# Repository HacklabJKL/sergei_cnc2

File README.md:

Sergei 2 CNC machine project
============================

This repository contains design files for Hacklab Jyväskylä's CNC machine project.
The machine is built out of existing linear assemblies that have been donated to us, and as such it is not readily reproducible. But some of the modules may be useful and in any case this repository contains information for future maintenance of the machine.

The machine design is a compromise between router and mill designs.
In general router-type CNC machines are more useful for our typical projects, as they have larger work area for flat stock.
But in the same time it would be desirable for the machine to be sturdy enough to cut mild steel at reasonable speeds.

The basic design is similar to fixed gantry routers or a portal milling machine.
X axis ballscrew assembly moves up and down on two Z axis columns.
Y axis moves the table.

Documentation index
-------------------

* [Parts list](PARTS.md)
* [Wiring diagram](electronics/wiring/images/sergei2-wiring.pdf)
* [Usage instructions (wiki)](https://github.com/HacklabJKL/sergei_cnc2/wiki)

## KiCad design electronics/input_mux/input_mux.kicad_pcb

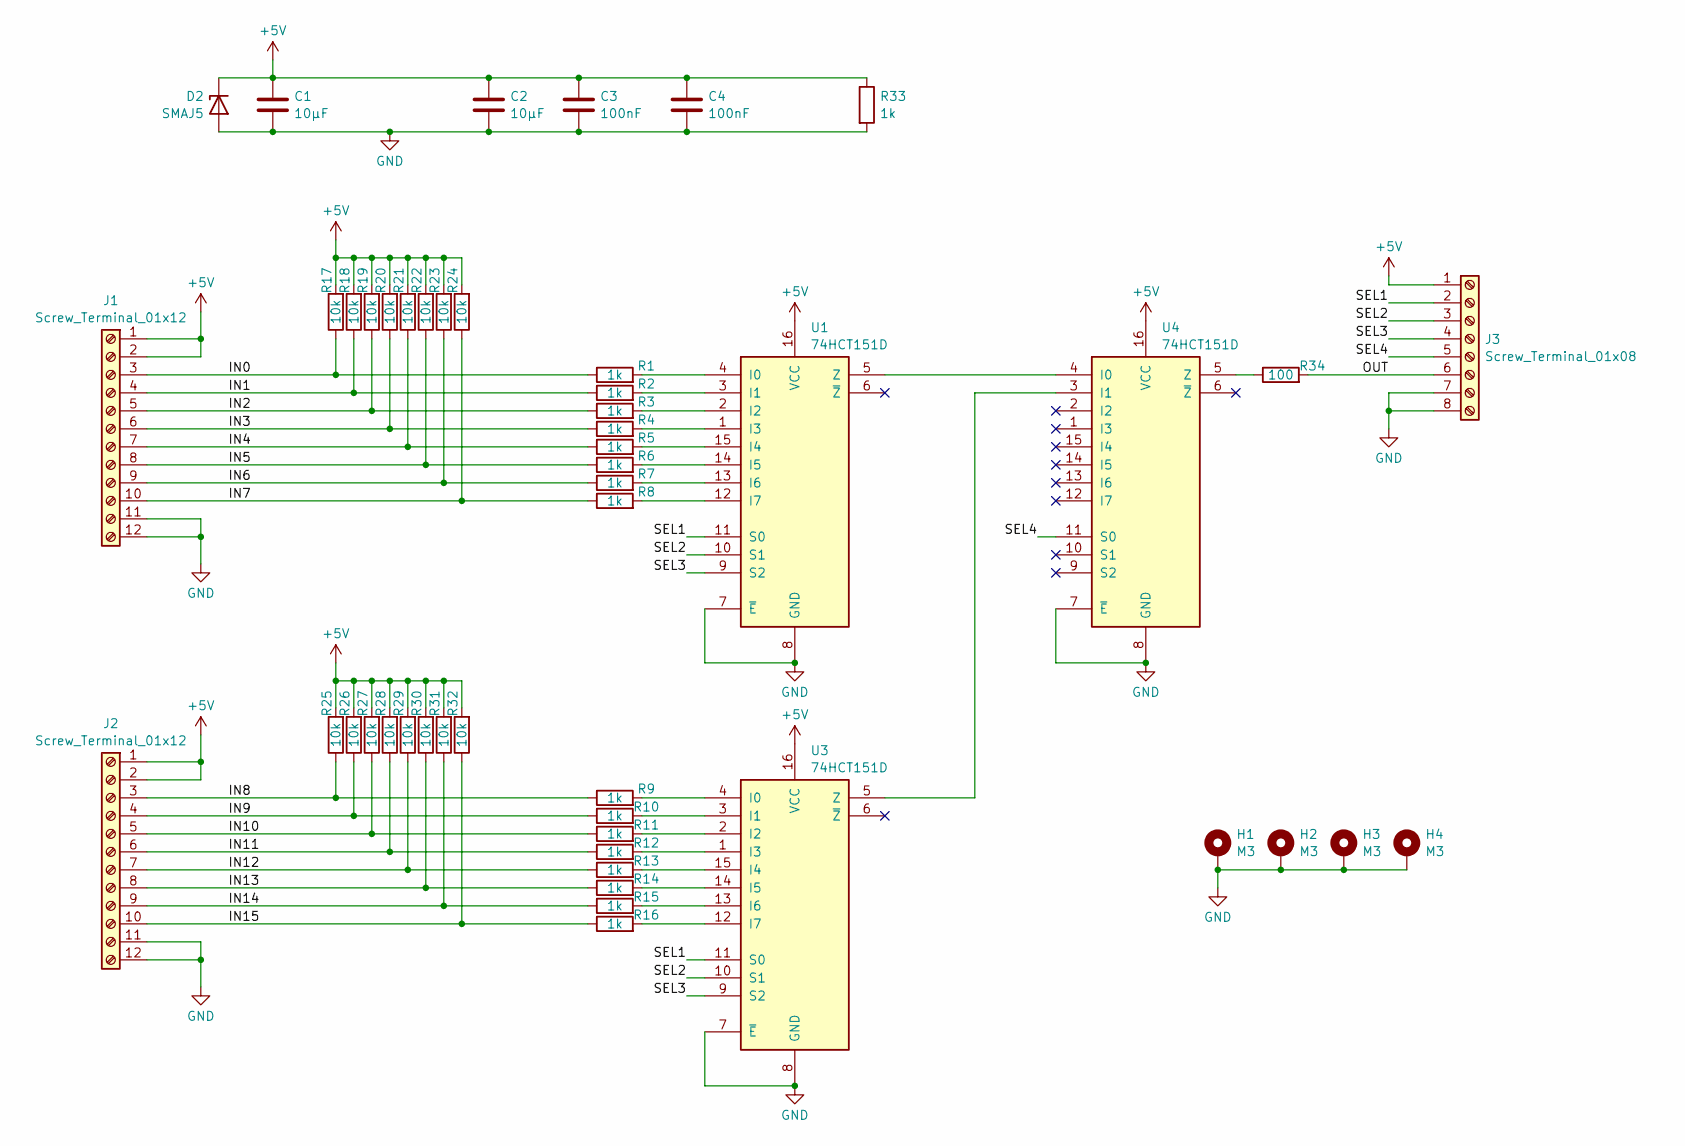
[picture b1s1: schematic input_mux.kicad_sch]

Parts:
C1, C2: 10µF; C_0805_2012Metric
C3, C4: 100nF; C_0805_2012Metric
D2: SMAJ5; D_SMA
H1, H2, H3, H4: M3; MountingHole_3.2mm_M3_Pad
J1, J2: Screw_Terminal_01x12; TerminalBlock_RND_205-00022_1x12_P5.00mm_Horizontal
J3: Screw_Terminal_01x08; TerminalBlock_RND_205-00018_1x08_P5.00mm_Horizontal
R1, R2, R3, R4, R5, R6, R7, R8, R9, R10, R11, R12, R13, R14, R15, R16, R33: 1k; R_0805_2012Metric
R17, R18, R19, R20, R21, R22, R23, R24, R25, R26, R27, R28, R29, R30, R31, R32: 10k; R_0805_2012Metric
R34: 100; R_0805_2012Metric
U1, U3, U4: 74HCT151D; SOIC-16_3.9x9.9mm_P1.27mm

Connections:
+5V: C1.1, C2.1, C3.1, C4.1, D2.1 (K), J1.1, J1.2, J2.1, J2.2, J3.1, R17.2, R18.2, R19.2, R20.2, R21.2, R22.2, R23.2, R24.2, R25.2, R26.2, R27.2, R28.2, R29.2, R30.2, R31.2, R32.2, R33.1, U1.16 (VCC), U3.16 (VCC), U4.16 (VCC)
/IN0: J1.3, R1.1, R17.1
/IN1: J1.4, R2.1, R18.1
/IN2: J1.5, R3.1, R19.1
/IN3: J1.6, R4.1, R20.1
/IN4: J1.7, R5.1, R21.1
/IN5: J1.8, R6.1, R22.1
/IN6: J1.9, R7.1, R23.1
/IN7: J1.10, R8.1, R24.1
/IN8: J2.3, R9.1, R25.1
/IN9: J2.4, R10.1, R26.1
/IN10: J2.5, R11.1, R27.1
/IN11: J2.6, R12.1, R28.1
/IN12: J2.7, R13.1, R29.1
/IN13: J2.8, R14.1, R30.1
/IN14: J2.9, R15.1, R31.1
/IN15: J2.10, R16.1, R32.1
/OUT: J3.6, R34.2
/SEL1: J3.2, U1.11 (S0), U3.11 (S0)
/SEL2: J3.3, U1.10 (S1), U3.10 (S1)
/SEL3: J3.4, U1.9 (S2), U3.9 (S2)
/SEL4: J3.5, U4.11 (S0)
GND: C1.2, C2.2, C3.2, C4.2, D2.2 (A), H1.1, H2.1, H3.1, H4.1, J1.11, J1.12, J2.11, J2.12, J3.7, J3.8, R33.2, U1.7 (~E), U1.8 (GND), U3.7 (~E), U3.8 (GND), U4.7 (~E), U4.8 (GND)
unnamed: R1.2, U1.4 (I0)
unnamed: R2.2, U1.3 (I1)
unnamed: R3.2, U1.2 (I2)
unnamed: R4.2, U1.1 (I3)
unnamed: R5.2, U1.15 (I4)
unnamed: R6.2, U1.14 (I5)
unnamed: R7.2, U1.13 (I6)
unnamed: R8.2, U1.12 (I7)
unnamed: U1.5 (Z), U4.4 (I0)
unnamed: R9.2, U3.4 (I0)
unnamed: R10.2, U3.3 (I1)
unnamed: R11.2, U3.2 (I2)
unnamed: R12.2, U3.1 (I3)
unnamed: R13.2, U3.15 (I4)
unnamed: R14.2, U3.14 (I5)
unnamed: R15.2, U3.13 (I6)
unnamed: R16.2, U3.12 (I7)
unnamed: U3.5 (Z), U4.3 (I1)
unnamed: R34.1, U4.5 (Z)

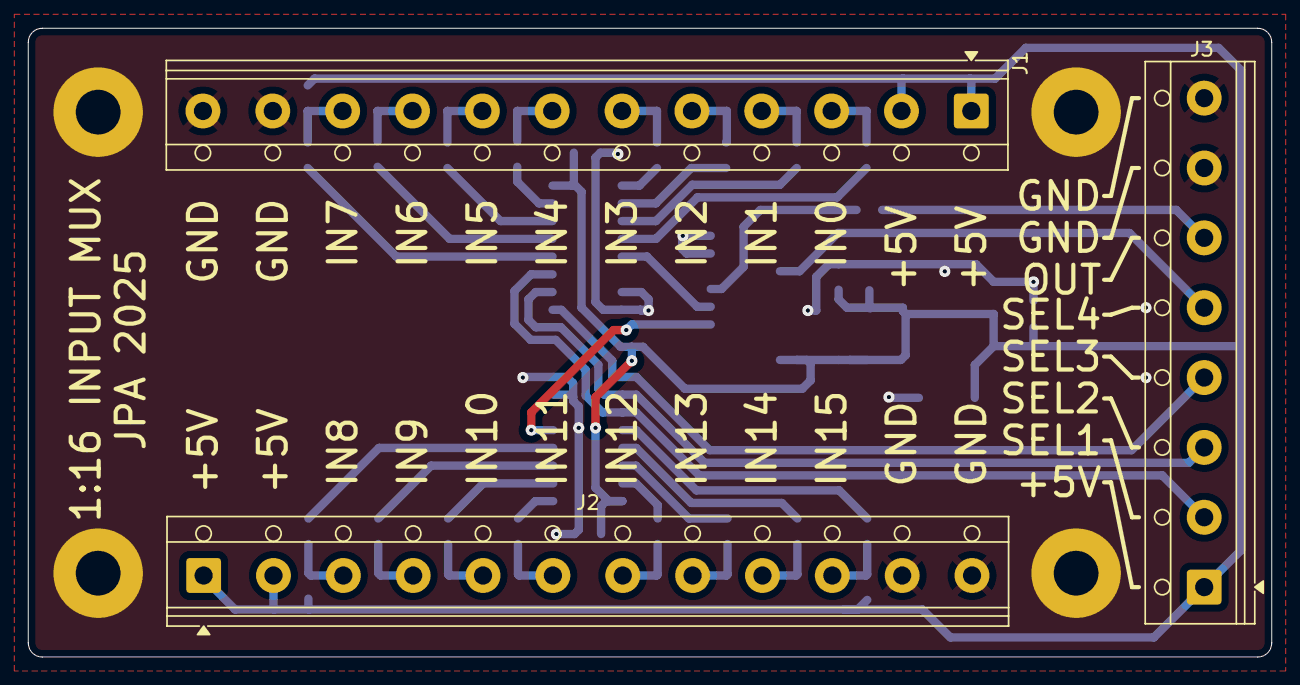
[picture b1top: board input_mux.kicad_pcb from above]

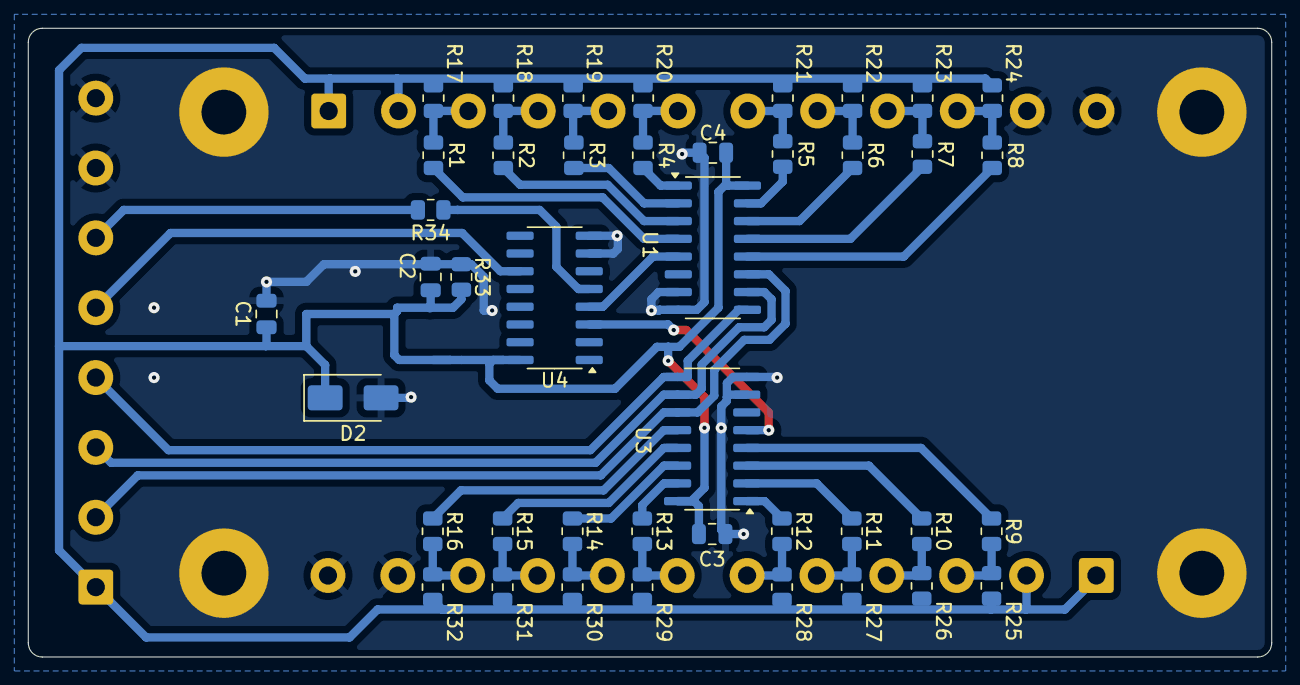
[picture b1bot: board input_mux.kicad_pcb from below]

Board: 2 copper layers, 89.0 x 45.0 mm, 49 parts (42 on the bottom side), 42 nets.

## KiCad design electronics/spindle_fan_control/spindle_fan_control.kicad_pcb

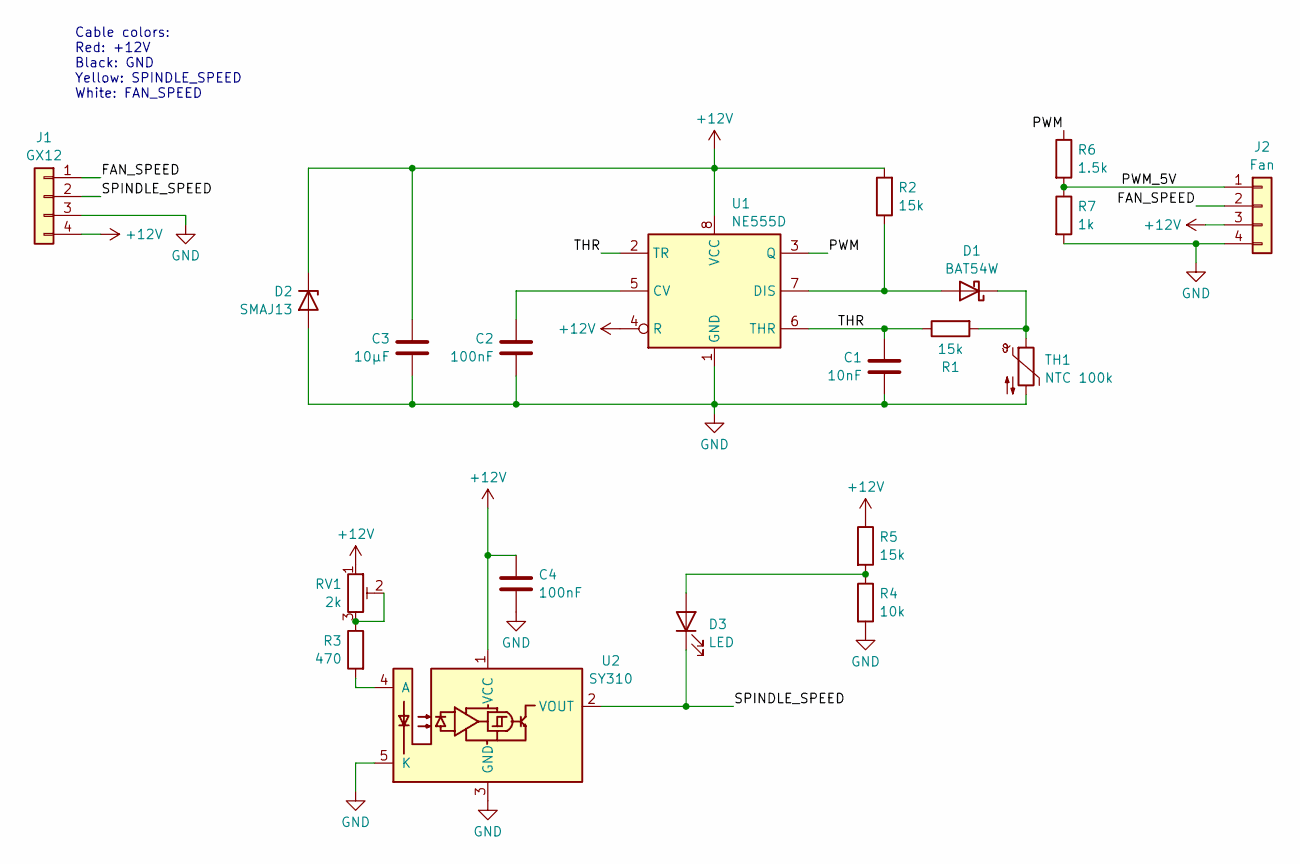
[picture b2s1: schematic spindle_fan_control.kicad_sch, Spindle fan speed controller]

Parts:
C1: 10nF; C_0603_1608Metric
C2, C4: 100nF; C_0603_1608Metric
C3: 10µF; C_0805_2012Metric
D1: BAT54W; D_SOD-123
D2: SMAJ13; D_SMA
D3: LED; D_0603_1608Metric
J1: GX12; PinHeader_2x02_P2.54mm_Vertical
J2: Fan; PinHeader_1x04_P2.54mm_Horizontal
R1, R2, R5: 15k; R_0603_1608Metric
R3: 470; R_0603_1608Metric
R4: 10k; R_0603_1608Metric
R6: 1.5k; R_0603_1608Metric
R7: 1k; R_0603_1608Metric
RV1: 2k; Potentiometer_Bourns_TC33X_Vertical
TH1: NTC 100k; PinHeader_1x02_P2.54mm_Vertical
U1: NE555D; SOIC-8_3.9x4.9mm_P1.27mm
U2: SY310; Kodenshi_LG206D

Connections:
+12V: C3.2, C4.2, D2.1 (K), J1.4, J2.3, R2.2, R5.1, RV1.1, U1.4 (R), U1.8 (VCC), U2.1 (VCC)
/FAN_SPEED: J1.1, J2.2
/PWM: R6.1, U1.3 (Q)
/PWM_5V: J2.1, R6.2, R7.1
/SPINDLE_SPEED: D3.1 (K), J1.2, U2.2 (VOUT)
/THR: C1.1, R1.1, U1.2 (TR), U1.6 (THR)
GND: C1.2, C2.1, C3.1, C4.1, D2.2 (A), J1.3, J2.4, R4.2, R7.2, TH1.2, U1.1 (GND), U2.3 (GND), U2.5 (K)
unnamed: D1.2 (A), R2.1, U1.7 (DIS)
unnamed: D1.1 (K), R1.2, TH1.1
unnamed: D3.2 (A), R4.1, R5.2
unnamed: R3.1, RV1.2, RV1.3
unnamed: C2.2, U1.5 (CV)
unnamed: R3.2, U2.4 (A)

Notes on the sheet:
Cable colors: Red: +12V Black: GND Yellow: SPINDLE_SPEED White: FAN_SPEED

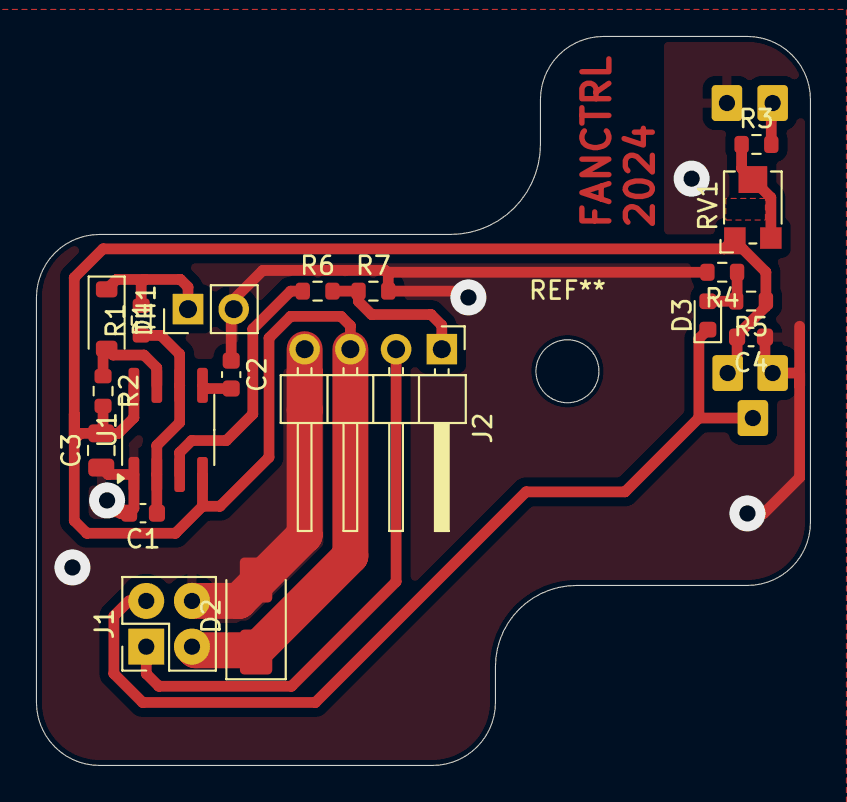
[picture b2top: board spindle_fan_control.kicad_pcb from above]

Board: 2 copper layers, 43.0 x 40.5 mm, 20 parts (1 on the bottom side), 13 nets.

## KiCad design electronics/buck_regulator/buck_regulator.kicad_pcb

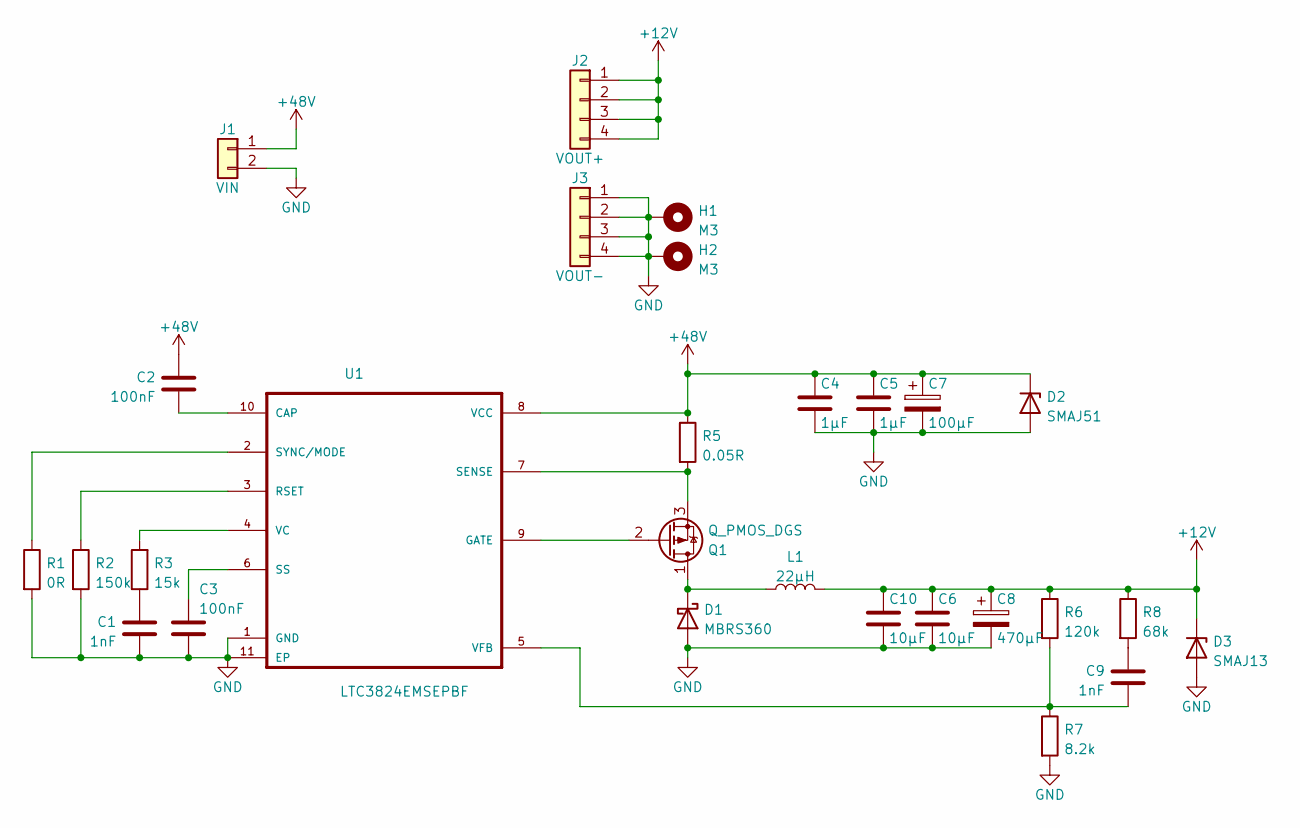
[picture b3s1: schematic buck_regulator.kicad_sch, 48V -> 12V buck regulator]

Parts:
C1, C9: 1nF; C_0603_1608Metric
C2, C3: 100nF; C_0603_1608Metric
C4, C5: 1µF; C_1210_3225Metric
C6, C10: 10µF; C_1206_3216Metric
C7: 100µF; CP_Radial_D10.0mm_P5.00mm
C8: 470µF; CP_Radial_D10.0mm_P5.00mm
D1: MBRS360; D_SMC
D2: SMAJ51; D_SMA
D3: SMAJ13; D_SMA
H1, H2: M3; MountingHole_3.2mm_M3_Pad
J1: VIN; TerminalBlock_Phoenix_PT-1,5-2-5.0-H_1x02_P5.00mm_Horizontal
J2: VOUT+; TerminalBlock_Phoenix_PT-1,5-4-5.0-H_1x04_P5.00mm_Horizontal
J3: VOUT-; TerminalBlock_Phoenix_PT-1,5-4-5.0-H_1x04_P5.00mm_Horizontal
L1: 22µH; L_Wuerth_HCM-1390
Q1: Q_PMOS_DGS; TSM680P06
R1: 0R; R_0603_1608Metric
R2: 150k; R_0603_1608Metric
R3: 15k; R_0603_1608Metric
R5: 0.05R; R_2512_6332Metric
R6: 120k; R_0603_1608Metric
R7: 8.2k; R_0603_1608Metric
R8: 68k; R_0603_1608Metric
U1: LTC3824EMSEPBF; MSOP-10-1EP_3x3mm_P0.5mm_EP1.68x1.88mm

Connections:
+12V: C6.1, C8.1, C10.1, D3.1 (K), J2.1, J2.2, J2.3, J2.4, L1.2, R6.1, R8.1
+48V: C2.1, C4.1, C5.1, C7.1, D2.1 (K), J1.1, R5.1, U1.8 (VCC)
GND: C1.2, C3.2, C4.2, C5.2, C6.2, C7.2, C8.2, C10.2, D1.2 (A), D2.2 (A), D3.2 (A), H1.1, H2.1, J1.2, J3.1, J3.2, J3.3, J3.4, R1.2, R2.2, R7.2, U1.1 (GND), U1.11 (EP)
unnamed: C1.1, R3.1
unnamed: C2.2, U1.10 (CAP)
unnamed: C3.1, U1.6 (SS)
unnamed: C9.1, R8.2
unnamed: C9.2, R6.2, R7.1, U1.5 (VFB)
unnamed: D1.1 (K), L1.1, Q1.1 (D)
unnamed: Q1.2 (G), U1.9 (GATE)
unnamed: Q1.3 (S), R5.2, U1.7 (SENSE)
unnamed: R1.1, U1.2 (SYNC/MODE)
unnamed: R2.1, U1.3 (RSET)
unnamed: R3.2, U1.4 (VC)

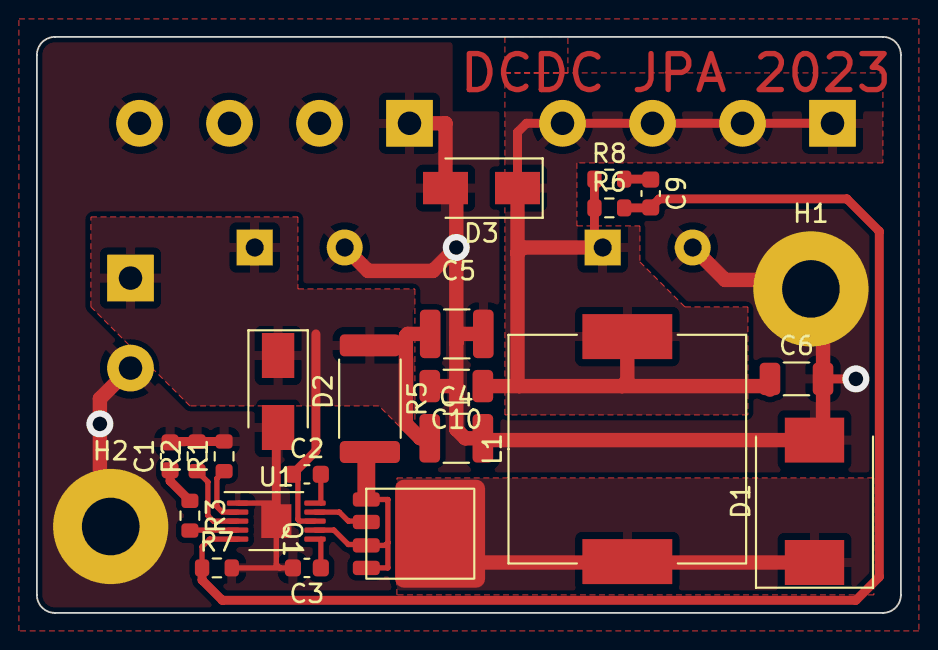
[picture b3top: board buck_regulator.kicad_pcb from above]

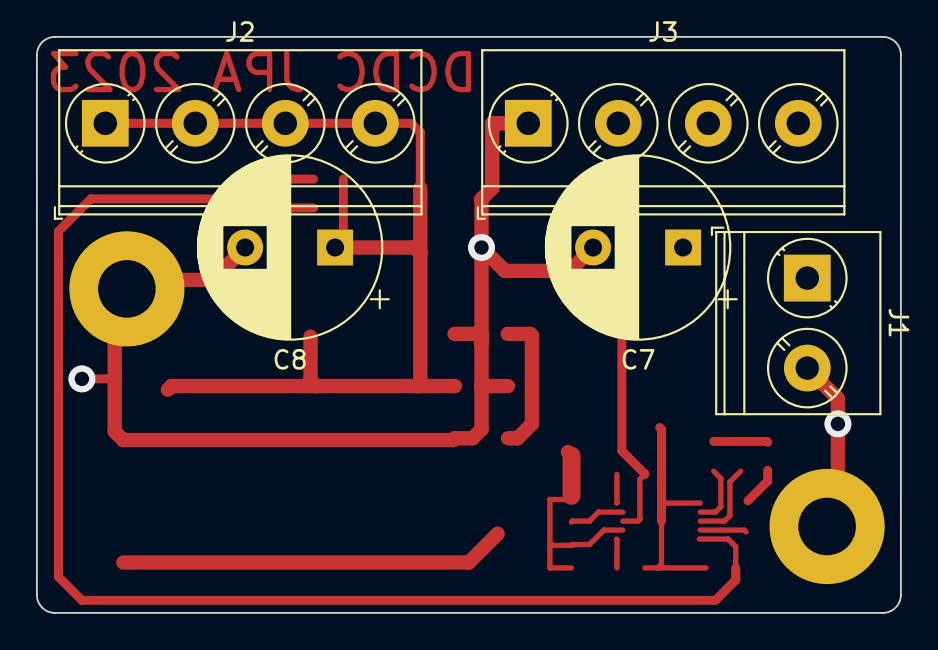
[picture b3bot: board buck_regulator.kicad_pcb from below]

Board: 2 copper layers, 48.0 x 32.0 mm, 28 parts (5 on the bottom side), 14 nets.

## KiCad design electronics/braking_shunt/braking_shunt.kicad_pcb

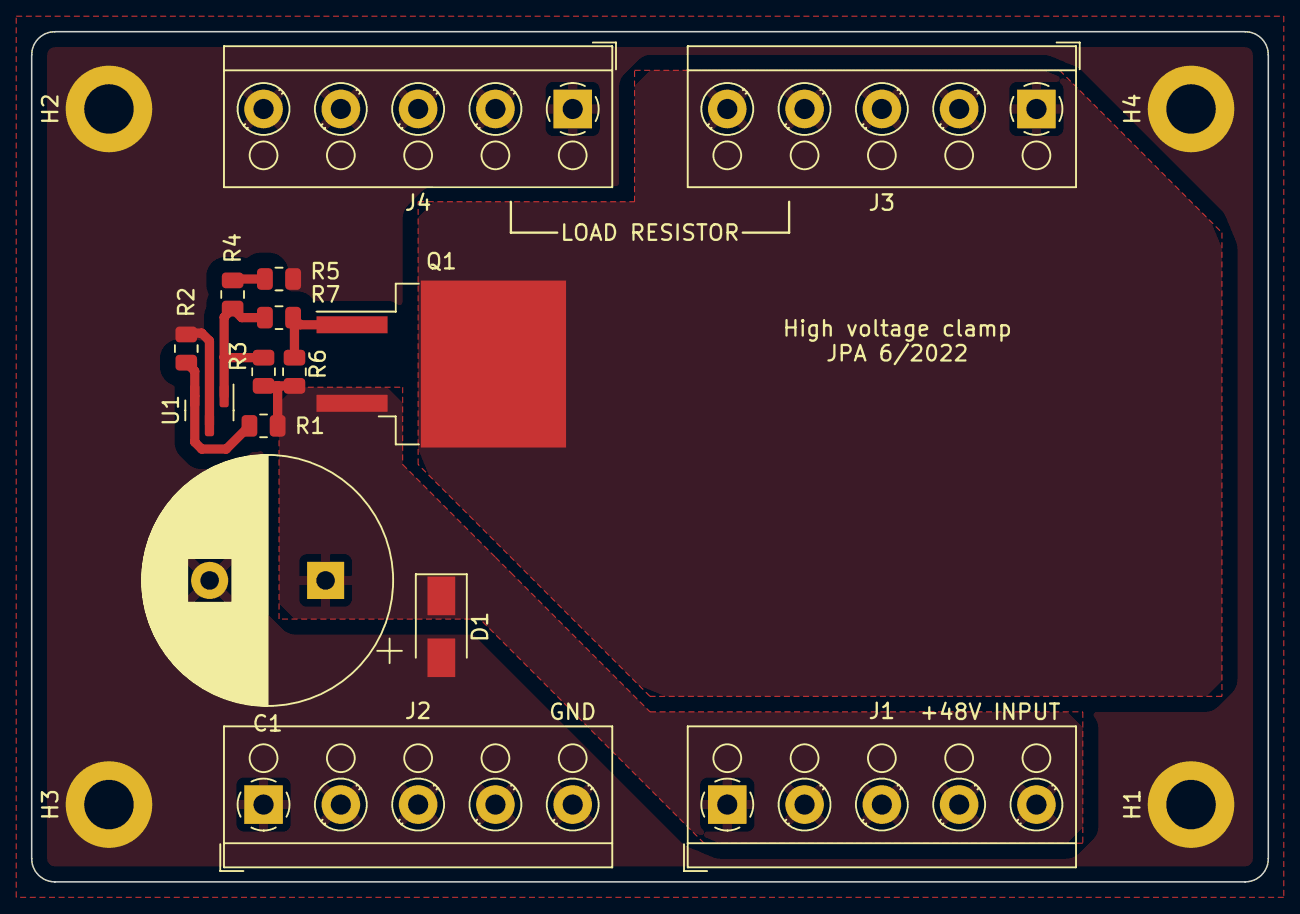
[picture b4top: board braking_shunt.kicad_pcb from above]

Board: 2 copper layers, 80.0 x 55.0 mm, 19 parts (0 on the bottom side), 7 nets.

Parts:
C1: 680µF; CP_Radial_D16.0mm_P7.50mm
D1: SMAJ51A; D_SMA
H1, H2, H3, H4: M3; MountingHole_3.2mm_M3_DIN965_Pad
J1: +48V; TerminalBlock_RND_205-00004_1x05_P5.00mm_Horizontal
J2: GND; TerminalBlock_RND_205-00004_1x05_P5.00mm_Horizontal
J3: LOAD_R+; TerminalBlock_RND_205-00004_1x05_P5.00mm_Horizontal
J4: LOAD_R-; TerminalBlock_RND_205-00004_1x05_P5.00mm_Horizontal
Q1: IRF4905S; TO-263-2
R1: 200k; R_0805_2012Metric
R2, R3, R4, R5: 10k; R_0805_2012Metric
R6: 100k; R_0805_2012Metric
R7: 470k; R_0805_2012Metric
U1: TL431DBZ; SOT-23

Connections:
+48V: C1.1, D1.1 (K), J1.1, J1.2, J1.3, J1.4, J1.5, Q1.3 (S), R1.1, R3.1, R6.1
/LOAD: J3.1, J3.2, J3.3, J3.4, J3.5, Q1.2 (D)
GND: C1.2, D1.2 (A), H1.1, H2.1, H3.1, H4.1, J2.1, J2.2, J2.3, J2.4, J2.5, J4.1, J4.2, J4.3, J4.4, J4.5, R2.2, R5.2, U1.3 (A)
unnamed: Q1.1 (G), R6.2, R7.1
unnamed: R1.2, R2.1, U1.2 (REF)
unnamed: R3.2, R4.1, R7.2, U1.1 (K)
unnamed: R4.2, R5.1

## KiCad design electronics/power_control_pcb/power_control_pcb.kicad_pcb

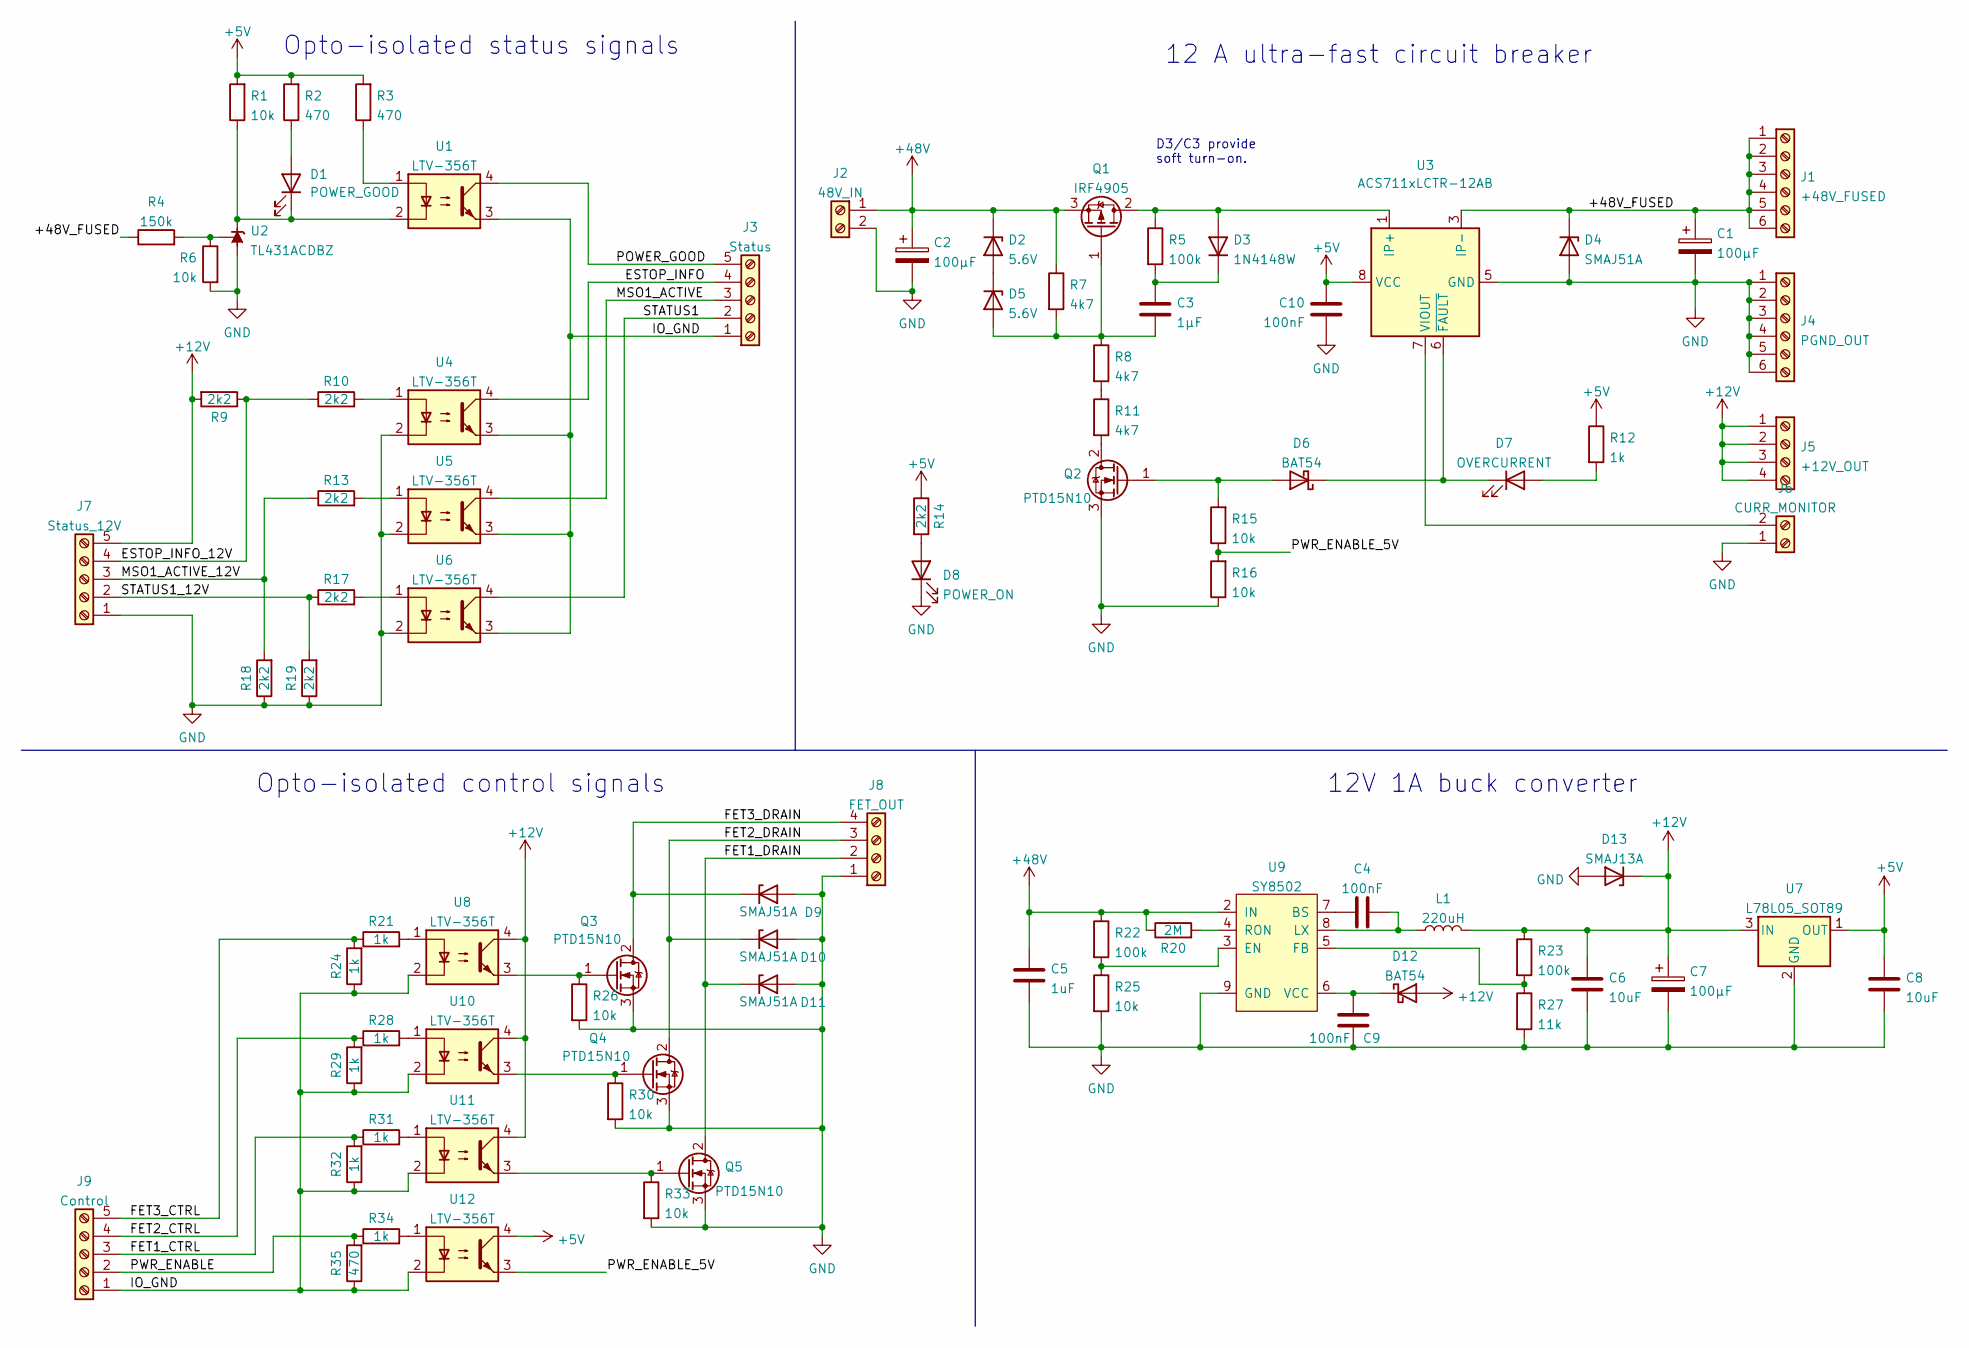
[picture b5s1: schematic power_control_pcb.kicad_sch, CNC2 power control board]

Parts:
C1, C2, C7: 100µF; CP_Radial_D10.0mm_P5.00mm
C3: 1µF; C_1210_3225Metric
C4, C9, C10: 100nF; C_0603_1608Metric
C5: 1uF; C_1210_3225Metric
C6, C8: 10uF; C_0805_2012Metric
D1: POWER_GOOD; LED_D3.0mm
D2, D5: 5.6V; D_SOD-123
D3: 1N4148W; D_SOD-123
D4, D9, D10, D11: SMAJ51A; D_SMA
D6, D12: BAT54; D_SOD-123
D7: OVERCURRENT; LED_D3.0mm
D8: POWER_ON; LED_D3.0mm
D13: SMAJ13A; D_SMA
J1: +48V_FUSED; TerminalBlock_Phoenix_MKDS-1,5-6_1x06_P5.00mm_Horizontal
J2: 48V_IN; TerminalBlock_Phoenix_MKDS-1,5-2_1x02_P5.00mm_Horizontal
J3: Status; TerminalBlock_TE_282834-5_1x05_P2.54mm_Horizontal
J4: PGND_OUT; TerminalBlock_Phoenix_MKDS-1,5-6_1x06_P5.00mm_Horizontal
J5: +12V_OUT; TerminalBlock_Phoenix_MKDS-1,5-4_1x04_P5.00mm_Horizontal
J6: CURR_MONITOR; TerminalBlock_Phoenix_MKDS-1,5-2_1x02_P5.00mm_Horizontal
J7: Status_12V; TerminalBlock_TE_282834-5_1x05_P2.54mm_Horizontal
J8: FET_OUT; TerminalBlock_Phoenix_MKDS-1,5-4_1x04_P5.00mm_Horizontal
J9: Control; TerminalBlock_TE_282834-5_1x05_P2.54mm_Horizontal
L1: 220uH; L_12x12mm_H6mm
Q1: IRF4905; TO-263-3_TabPin2
Q2, Q3, Q4, Q5: PTD15N10; TO-252-2
R1, R6, R15, R16, R25, R26, R30, R33: 10k; R_0603_1608Metric
R2, R3, R35: 470; R_0603_1608Metric
R4: 150k; R_0603_1608Metric
R5, R22, R23: 100k; R_0603_1608Metric
R7, R8, R11: 4k7; R_0603_1608Metric
R9, R10, R13, R14, R17, R18, R19: 2k2; R_0603_1608Metric
R12, R21, R24, R28, R29, R31, R32, R34: 1k; R_0603_1608Metric
R20: 2M; R_0603_1608Metric
R27: 11k; R_0603_1608Metric
U1, U4, U5, U6, U8, U10, U11, U12: LTV-356T; SO-4_4.4x3.6mm_P2.54mm
U2: TL431ACDBZ; SOT-23
U3: ACS711xLCTR-12AB; SOIC-8_3.9x4.9mm_P1.27mm
U7: L78L05_SOT89; SOT-89-3
U9: SY8502; SOIC-8-1EP_3.9x4.9mm_P1.27mm_EP2.29x3mm

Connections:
+5V: C8.1, C10.1, R1.2, R2.2, R3.2, R12.1, R14.1, U3.8 (VCC), U7.1 (OUT), U12.4
+12V: C6.1, C7.1, D12.2 (A), D13.1 (K), J5.1, J5.2, J5.3, J5.4, J7.5, L1.2, R9.2, R23.1, U7.3 (IN), U8.4, U10.4, U11.4
+48V: C2.1, C5.1, D2.1 (K), J2.1, Q1.3 (S), R7.1, R20.1, R22.1, U9.2 (IN)
/+48V_FUSED: C1.1, D4.1 (K), J1.1, J1.2, J1.3, J1.4, J1.5, J1.6, R4.1, U3.3 (IP-), U3.4 (IP-)
/ESTOP_INFO: J3.4, U4.4
/ESTOP_INFO_12V: J7.4, R9.1, R10.1
/FET1_CTRL: J9.3, R31.1, R32.2
/FET1_DRAIN: D11.1 (K), J8.2, Q5.2 (D)
/FET2_CTRL: J9.4, R28.1, R29.2
/FET2_DRAIN: D10.1 (K), J8.3, Q4.2 (D)
/FET3_CTRL: J9.5, R21.1, R24.2
/FET3_DRAIN: D9.1 (K), J8.4, Q3.2 (D)
/IO_GND: J3.1, J9.1, R24.1, R29.1, R32.1, R35.1, U1.3, U4.3, U5.3, U6.3, U8.2, U10.2, U11.2, U12.2
/MSO1_ACTIVE: J3.3, U5.4
/MSO1_ACTIVE_12V: J7.3, R13.1, R18.2
/POWER_GOOD: J3.5, U1.4
/PWR_ENABLE: J9.2, R34.1, R35.2
/PWR_ENABLE_5V: R15.1, R16.2, U12.3
/STATUS1: J3.2, U6.4
/STATUS1_12V: J7.2, R17.1, R19.2
GND: C1.2, C2.2, C5.2, C6.2, C7.2, C8.2, C9.2, C10.2, D4.2 (A), D8.1 (K), D9.2 (A), D10.2 (A), D11.2 (A), D13.2 (A), J2.2, J4.1, J4.2, J4.3, J4.4, J4.5, J4.6, J6.1, J7.1, J8.1, Q2.3 (S), Q3.3 (S), Q4.3 (S), Q5.3 (S), R6.2, R16.1, R18.1, R19.1, R25.2, R26.2, R27.2, R30.2, R33.2, U2.3 (A), U3.5 (GND), U4.2, U5.2, U6.2, U7.2 (GND), U9.9 (GND)
unnamed: C3.1, D3.1 (K), R5.2
unnamed: C3.2, D5.2 (A), Q1.1 (G), R7.2, R8.1
unnamed: C4.1, U9.7 (BS)
unnamed: C4.2, L1.1, U9.8 (LX)
unnamed: C9.1, D12.1 (K), U9.6 (VCC)
unnamed: D1.1 (K), R1.1, U1.2, U2.1 (K)
unnamed: D1.2 (A), R2.1
unnamed: D2.2 (A), D5.1 (K)
unnamed: D3.2 (A), Q1.2 (D), R5.1, U3.1 (IP+), U3.2 (IP+)
unnamed: D6.1 (K), D7.1 (K), U3.6 (~FAULT)
unnamed: D6.2 (A), Q2.1 (G), R15.2
unnamed: D7.2 (A), R12.2
unnamed: D8.2 (A), R14.2
unnamed: J6.2, U3.7 (VIOUT)
unnamed: Q2.2 (D), R11.2
unnamed: Q3.1 (G), R26.1, U8.3
unnamed: Q4.1 (G), R30.1, U10.3
unnamed: Q5.1 (G), R33.1, U11.3
unnamed: R3.1, U1.1
unnamed: R4.2, R6.1, U2.2 (REF)
unnamed: R10.2, U4.1
unnamed: R8.2, R11.1
unnamed: R13.2, U5.1
unnamed: R17.2, U6.1
unnamed: R20.2, U9.4 (RON)
unnamed: R21.2, U8.1
unnamed: R22.2, R25.1, U9.3 (EN)
unnamed: R23.2, R27.1, U9.5 (FB)
unnamed: R28.2, U10.1
unnamed: R31.2, U11.1
unnamed: R34.2, U12.1

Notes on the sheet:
Opto-isolated control signals
12V 1A buck converter
12 A ultra-fast circuit breaker
D3/C3 provide soft turn-on.
Opto-isolated status signals

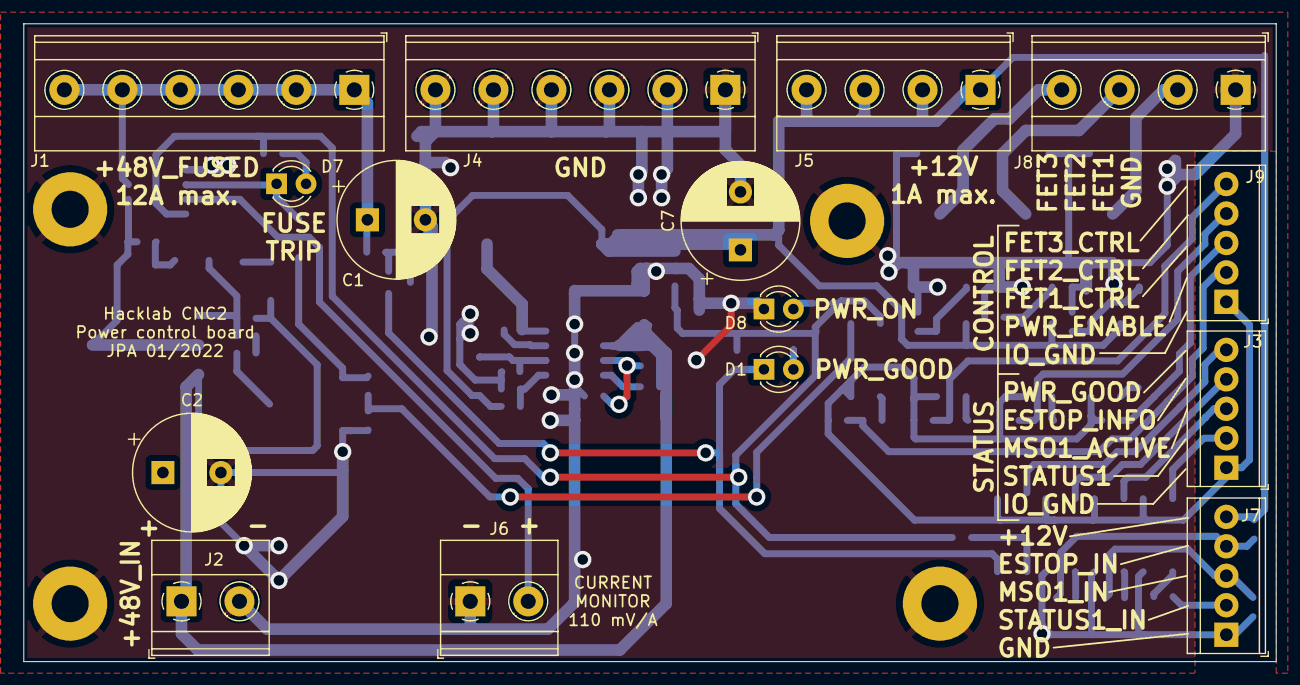
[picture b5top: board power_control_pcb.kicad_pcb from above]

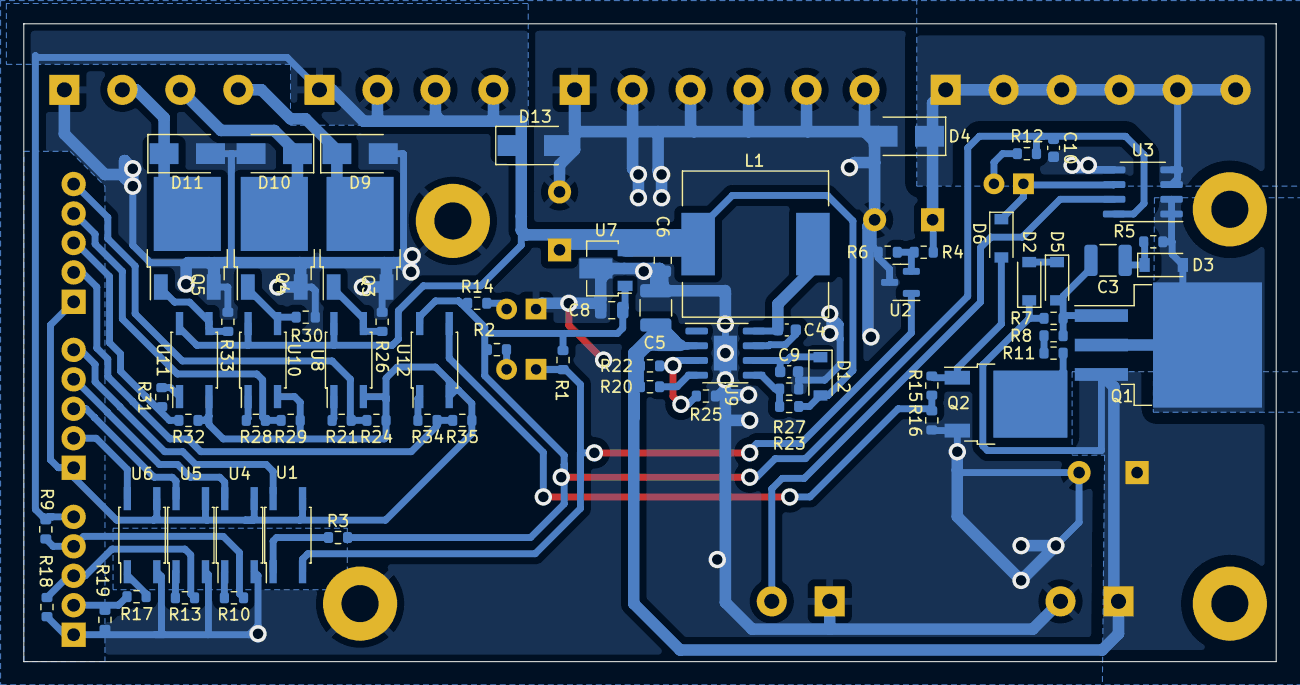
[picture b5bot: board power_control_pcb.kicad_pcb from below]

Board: 2 copper layers, 108.0 x 55.0 mm, 85 parts (70 on the bottom side), 52 nets.
